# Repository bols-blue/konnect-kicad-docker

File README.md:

# konnect-kicad-docker

Konnect(KiCad 用 MCP サーバ)と KiCad 10 の CLI を 1 イメージに同梱し、
Claude Code から **回路図生成 → ERC → 製造ファイル出力** まで回すための検証環境。

PCB のインタラクティブ編集(部品配置・配線)は KiCad の GUI プロセスを必要とする。
ローカルのデスクトップ環境では `make gui` で同じイメージの KiCad GUI を X11 転送で
起動し、その IPC ソケットを Konnect と共有することで PCB 系ツールも使える。

## 使い方(Claude Code)

プラグイン `kicad-konnect` として入れると、どのディレクトリでも使える。

```bash
# 1. Docker イメージを取得 (初回のみ)
docker pull ghcr.io/bols-blue/konnect-kicad:10
docker tag ghcr.io/bols-blue/konnect-kicad:10 konnect-kicad:10

# 2. プラグインをインストール (Claude Code 内の /plugin からでも可)
claude plugin marketplace add bols-blue/konnect-kicad-docker
claude plugin install kicad-konnect@konnect-kicad

# 3. 作業ディレクトリで起動 (このディレクトリがコンテナの /work になる)
mkdir -p ~/kicad-work && cd ~/kicad-work && git init
claude
```

1. `/mcp` で `plugin:kicad-konnect:konnect` が connected になっていることを確認する
2. 「/work/demo に KiCad プロジェクトを作って、抵抗を 1 つ置いて ERC して」のように頼む
   - KiCad の話をすればスキルは自動で読み込まれる
   - `/kicad-konnect:kicad-konnect` で明示的に呼ぶこともできる

**作業領域の指定:**
- `/work` にする場所は `KONNECT_PROJECTS=/path/to/dir claude` で変えられる
- ホームディレクトリ直下や `/` で起動すると、安全のため konnect は起動しない

**PCB 編集・自動配線(GUI が必要):** 次の順で操作する。起動コマンドは Claude に聞けば、インストール先のパスで教えてくれる。
1. プラグインの `scripts/kicad-gui.sh /work/<name>/<name>.kicad_pro` で KiCad GUI を起動する
2. PCB エディタで基板を開く
3. `/mcp` で konnect を再接続する
   - native Specctra ブリッジ(自動配線用の DSN 出力・SES 取り込み)を使うときは必須
   - GUI を起動し直したら、再接続もやり直す

**更新:** `claude plugin marketplace update konnect-kicad` のあと、プラグインを入れ直す。

**このリポジトリの中ではプラグインは不要:**
- ルートの `.mcp.json` とスキルへのリンクで動く(`/work` は `./projects`)
- プラグインを入れたままここで起動すると konnect が 2 つ立つので、`/plugin` で無効にする

Codex で使う場合や、構成の詳細は後述の「プラグインとして使う」を参照。

## 前提

- Docker(Compose v2 同梱のもの)、Linux x86_64(KiCad 公式イメージが amd64 のみ)
- ディスク空き 3 GB 程度(公開イメージを使う場合)/ 10 GB 程度(自前ビルドの場合)
- Claude Code

## セットアップ

公開イメージを使う(推奨):

```bash
make pull      # ghcr.io/bols-blue/konnect-kicad:10 を取得し konnect-kicad:10 としてタグ付け
make smoke     # 疎通確認
```

自前でビルドする:

```bash
make build     # 初回は Rust のフルビルドを含むため時間がかかる
make smoke
```

`make smoke` が全項目 OK になったら、このディレクトリで Claude Code を起動する。
`.mcp.json` がプロジェクトスコープの MCP 設定として読み込まれ、`konnect` サーバが
使えるようになる(初回は MCP サーバの承認プロンプトが出る)。

```bash
claude
```

Claude Code 側の動き方はスキル `plugins/kicad-konnect/skills/kicad-konnect/` に
書いてある(このリポジトリでは `.claude/skills/` から読み込まれる)。これが本体。
リポジトリ固有の約束は `CLAUDE.md`。

## プラグインとして使う(Claude Code / Codex)

このリポジトリは Claude Code と Codex のプラグインマーケットプレイスを兼ねている。
プラグイン `kicad-konnect` を入れると、どのディレクトリでもスキルと `konnect`
MCP サーバが使える。Docker イメージは別途必要(上の `make pull`、または
`docker pull ghcr.io/bols-blue/konnect-kicad:10 && docker tag ghcr.io/bols-blue/konnect-kicad:10 konnect-kicad:10`)。

Claude Code:

```bash
claude plugin marketplace add bols-blue/konnect-kicad-docker
claude plugin install kicad-konnect@konnect-kicad
```

Codex:

```bash
codex plugin marketplace add bols-blue/konnect-kicad-docker
# Codex の /plugins から kicad-konnect をインストール
```

**`/work` にマウントされるのはエージェントを起動したディレクトリ。** 環境変数
`KONNECT_PROJECTS` で上書きできる。ホームディレクトリ直下や `/` では安全のため
起動を拒否する。

- Claude Code: 起動ディレクトリ(`CLAUDE_PROJECT_DIR`)が既定
- Codex: MCP サーバがプラグインのディレクトリで起動されるため、起動ディレクトリを
  知る手段が無い。**`KONNECT_PROJECTS` の設定が必須**
  (例: `KONNECT_PROJECTS=$PWD codex`)。
  シェルのサンドボックスが Docker ソケットを塞ぐ
  (`permission denied while trying to connect to the docker API`、codex-cli 0.160.1 で確認)。
  `kicad-cli.sh` の実行時にサンドボックス外での実行を承認する
- Codex: konnect の MCP ツール呼び出しには承認が要る。`codex exec`(非対話)では
  承認できず `MCP tool call requires approval, but approval policy is never` で失敗する。
  `default_tools_approval_mode = "auto"` を設定しても変わらなかった。対話モードで使うこと

| 構成要素 | 場所 |
| --- | --- |
| Claude Code の manifest(MCP 設定込み) | `plugins/kicad-konnect/.claude-plugin/plugin.json` |
| Codex の manifest / MCP 設定 | `plugins/kicad-konnect/.codex-plugin/plugin.json` / `codex-mcp.json` |
| スキル | `plugins/kicad-konnect/skills/kicad-konnect/` |
| マーケットプレイス | `.claude-plugin/marketplace.json`(Claude Code)/ `.agents/plugins/marketplace.json`(Codex) |

IPC ソケットと GUI 設定は `~/.local/state/konnect-kicad/` に置く
(`KONNECT_IPC_DIR` / `KONNECT_GUI_CONFIG` で変更可)。

## ディレクトリ

```
.
├── Dockerfile              KiCad 公式イメージ + Konnect ビルド + Freerouting/Java
├── docker-compose.yml      バッチ用ワークベンチ(任意)
├── Makefile                pull / build / smoke / shell / gui
├── .github/workflows/      イメージのビルド・smoke test・GHCR 公開
├── .mcp.json               このリポジトリで作業するときの MCP 設定
├── CLAUDE.md               このリポジトリ固有の約束
├── .claude-plugin/         Claude Code のマーケットプレイス定義
├── .agents/plugins/        Codex のマーケットプレイス定義
├── .claude/skills/         スキルへのシンボリックリンク
├── plugins/kicad-konnect/  プラグイン本体
│   ├── .claude-plugin/     Claude Code の manifest
│   ├── .codex-plugin/      Codex の manifest (+ codex-mcp.json)
│   ├── skills/kicad-konnect/  スキル(可否の線引き・ルール・手順・既知の癖)
│   └── scripts/
│       ├── _env.sh         作業領域・IPC の場所の決定(共通)
│       ├── konnect-mcp.sh  MCP stdio 起動ラッパー
│       ├── kicad-cli.sh    ホストから kicad-cli を叩くラッパー
│       ├── kicad-gui.sh    KiCad GUI を X11 転送で起動 (PCB系ツール用)
│       └── smoke-test.sh   疎通確認
└── projects/               作業領域。make / .mcp.json 経由ではコンテナの /work にマウントされる
```

**このリポジトリでは、ホストの `./projects` がコンテナの `/work`。** Konnect に渡すパスは常に
`/work/...` 形式にする。

既存の KiCad プロジェクトを試すときは `projects/` の下に `git clone` する。
`projects/*/` はこのリポジトリの `.gitignore` で除外しているので、クローンした
リポジトリはそれ自身の git で管理する。ライブラリの絶対パスや KiCad 6 以前の
ファイル形式など、取り込み時に直すべき点はスキルの `references/import-existing.md` にまとめてある。

```bash
cd projects && git clone <repo-url>
```

## 設計上のポイント

**ランタイムに KiCad 公式イメージを使っている。** 公式イメージは kicad-cli 利用を
想定して配布されており、GUI 用途はサポート対象外と明示されている。この環境は
まさに CLI だけを使うので用途が一致する。

**Konnect はソースからビルドしている。** 配布バイナリは Windows / macOS 向けで、
Linux は公式にはロードマップ段階(コード自体は 3 プラットフォームで CI を通過)。
ビルダーはランタイム (Debian 13 trixie) より古い bookworm にして、新しい glibc 上で
そのまま動くバイナリにしている。

**グローバル `sym-lib-table` をイメージに焼いてある。** コンテナは毎回まっさらな
HOME で起動するため、これが無いとシンボル解決に失敗して ERC が通らない。
`make smoke` の項目 2 がここを見ている。

**コンテナは呼び出し元の UID で起動する。** ラッパースクリプトが
`--user $(id -u):$(id -g)` を渡しているので、`./projects` に root 所有の
ファイルが生えない。

## 事前に把握しておくべき制約

**PCB 系ツールは GUI 起動中のみ。** Konnect の PCB 編集は KiCad 10 の IPC API
(NNG + protobuf)経由で、KiCad が対象基板を PCB エディタで開いた状態で
動いている必要がある。

```bash
make gui PROJECT=/work/demo/demo.kicad_pro   # KiCad が X11 (Wayland なら XWayland) で開く
# → プロジェクトマネージャで PCB エディタを開く
make gui-stop
```

- IPC ソケットはホストの `./.kicad-ipc`(プラグインとして使うときは `~/.local/state/konnect-kicad/ipc`)を GUI / Konnect 両コンテナの
  `/tmp/kicad` にマウントして共有する。Konnect には `KICAD_API_SOCKET` で固定パスを渡す
  (Konnect のソケット自動検出は起動時に一度だけなので、GUI を後から起動しても繋がるように)
- GUI の設定は `./.kicad-gui-config`(プラグインでは `~/.local/state/konnect-kicad/gui-config`)に永続化する。初回だけセットアップウィザードが出る
  (完了するまで IPC サーバが起動しない)
- 公式イメージの GUI 利用はサポート外。フォント・IME・OpenGL で問題が出る可能性がある
- 動作確認済み: 回路図 → PCB 反映、フットプリント配置、外形追加、保存、
  DSN 出力 → Freerouting → SES 取り込み → DRC の通し(THT 部品の基板)。
  SMD 受動部品 (roundrect パッド) は Konnect が DSN 出力を拒否するので、
  DSN 出力と SES 取り込みは GUI で人が行う。詳細はスキルの可否表
- 自動配線は Freerouting 2.3.0(SHA-256 検証済み)+ OpenJDK 25 をイメージに同梱。
  Konnect が headless MCP モードで起動し、DSN → SES をローカルで処理する。
  起動時に GitHub へ新版チェックの通信が出る(`KONNECT_NETWORK=none` なら出ないが部品検索も止まる)
- ヘッドレス環境(SSH 先など)ではこの経路は使えない。回路図と ERC まで作って、
  あとはホストの KiCad に引き継ぐ

**Konnect は beta。** コアのツールチェーンは動作確認済みだが若いリリースで、
実地での検証を求めている段階。回路図ファイルを直接書き換えるので、必ず git 管理下の
コピーに対して使うこと。実案件のディレクトリを `./projects` にマウントしない。

**Konnect のライセンスは AGPL-3.0。** ホビイスト・学生・フリーランス・OSS は自由に使える一方、
企業の場合は Konnect の上や周辺に作ったものが、ネットワーク越しに提供する
ソフトウェアも含めて同ライセンスでのオープンソース化を要求される。商用ライセンスも
別途用意されている。個人の評価で閉じるなら問題にならないが、社内共有や業務利用に
広げる前に法務確認を入れること(法的判断は専門家に)。

**HTTP モードは有効にしていない。** Konnect のサーバには認証が無く、ツールは
ファイルを編集し kicad-cli を実行するため、上流でも compose はループバック限定で
公開している。この構成では stdio のみにしている。必要になったら認証付きの
リバースプロキシを前段に置き、`0.0.0.0` に素で公開しないこと。

## バージョン

中身のバージョンは Dockerfile の `ARG` 既定値で固定している(動作検証済みの組み合わせ)。

| 部品 | バージョン | 定義 |
| --- | --- | --- |
| KiCad | 10.0.6 | `KICAD_TAG` |
| Konnect | `9d582b6` (0.12.1) | `KONNECT_REF`(ブランチ・タグ・SHA いずれも可) |
| Freerouting | 2.3.0 | `FREEROUTING_VERSION` / `FREEROUTING_SHA256` |
| OpenJDK | 25 (Debian パッケージ) | Dockerfile |

別の組み合わせを試す場合:

```bash
make build KICAD_TAG=10.0.7 KONNECT_REF=<タグ or コミットSHA>
make smoke
```

検証できたら Dockerfile の既定値を更新して main に push すると、GitHub Actions が
smoke test を通したうえで GHCR に公開する。ビルド済みイメージのバージョンは
`make versions` で確認できる。

## 公開イメージ

`ghcr.io/bols-blue/konnect-kicad` に以下のタグで公開している
(`.github/workflows/image.yml`)。

| タグ | 内容 |
| --- | --- |
| `10` | main の最新 |
| `kicad<ver>-konnect<sha7>` | 中身のバージョンで固定したい場合 |
| `sha-<sha7>` | このリポジトリのコミット |
| `v*` | リリースタグ |

## 同梱ソフトウェアのライセンスとソース

イメージは以下を再配布している。いずれもソースは上流で公開されており、
同梱したバージョンは上の表とイメージのラベル(`docker inspect`)で特定できる。

| 部品 | ライセンス | ソース |
| --- | --- | --- |
| Konnect | AGPL-3.0-only | https://github.com/mixelpixx/Konnect (該当コミットは `/etc/konnect-commit.txt`) |
| KiCad | GPL-3.0-or-later | https://gitlab.com/kicad/code/kicad (ベースイメージ `kicad/kicad`) |
| Freerouting | GPL-3.0 | https://github.com/freerouting/freerouting |
| OpenJDK | GPL-2.0 with Classpath Exception | Debian パッケージ `openjdk-25-jre-headless` |
| Debian ベースの各パッケージ | 各パッケージによる | `apt-get source` で取得可 |

このリポジトリ自体(Dockerfile・スクリプト・ドキュメント)には上記のコードは含まれない。

## トラブルシュート

| 症状 | 対処 |
| --- | --- |
| `make build` がライブラリ検証で落ちる | KiCad イメージのディレクトリ構成が変わっている。エラー出力の `ls` 結果を見て Dockerfile のパスを修正 |
| Claude Code が konnect を認識しない | `claude mcp list` で状態を確認。`.mcp.json` の相対パスはプロジェクトルート基準。ダメなら `plugins/kicad-konnect/scripts/konnect-mcp.sh` を絶対パスに書き換える |
| `image not found` | `make pull` / `make build` 未実行、または `KONNECT_IMAGE` の値が `.mcp.json` と不一致 |
| ERC でシンボルが軒並み見つからない | `make smoke` の項目 2 を確認。`sym-lib-table=NO` なら Dockerfile の `KICAD_CONFIG_VER` を実際の設定ディレクトリ名に合わせる |
| `IPC connect failed` | KiCad GUI 未起動、または PCB エディタで対象基板を開いていない。`make gui`。プラグインとこのリポジトリの `.mcp.json` では IPC の置き場が違うので、GUI も同じ側から起動する |
| `make gui` で IPC ソケットが現れない | 初回ウィザードやダイアログで止まっていないか確認。`KONNECT_GUI_DEBUG=1 make gui` で前面実行 |
| `make` が「ターゲットを make するルールがありません」 | `projects/` の下で実行している。`make -C <このリポジトリ> gui ...` |
| クローンしたプロジェクトで ERC がライブラリ不足で大量に落ちる | プロジェクトの `sym-lib-table` / `fp-lib-table` がホストの絶対パスを指している。ライブラリをプロジェクト内にコピーし `${KIPRJMOD}` 基準にする |
| Konnect の回路図編集が `stale_target` で拒否される | KiCad 6 以前の回路図。KiCad GUI で開いて保存する(`kicad-cli sch upgrade` では直らない) |
| Rust ビルドが OOM で落ちる | Docker Desktop のメモリ割り当てを 8 GB 以上に |

## 参考

- Konnect: https://github.com/mixelpixx/Konnect
- KiCad 公式 Docker イメージ: https://www.kicad.org/download/docker/

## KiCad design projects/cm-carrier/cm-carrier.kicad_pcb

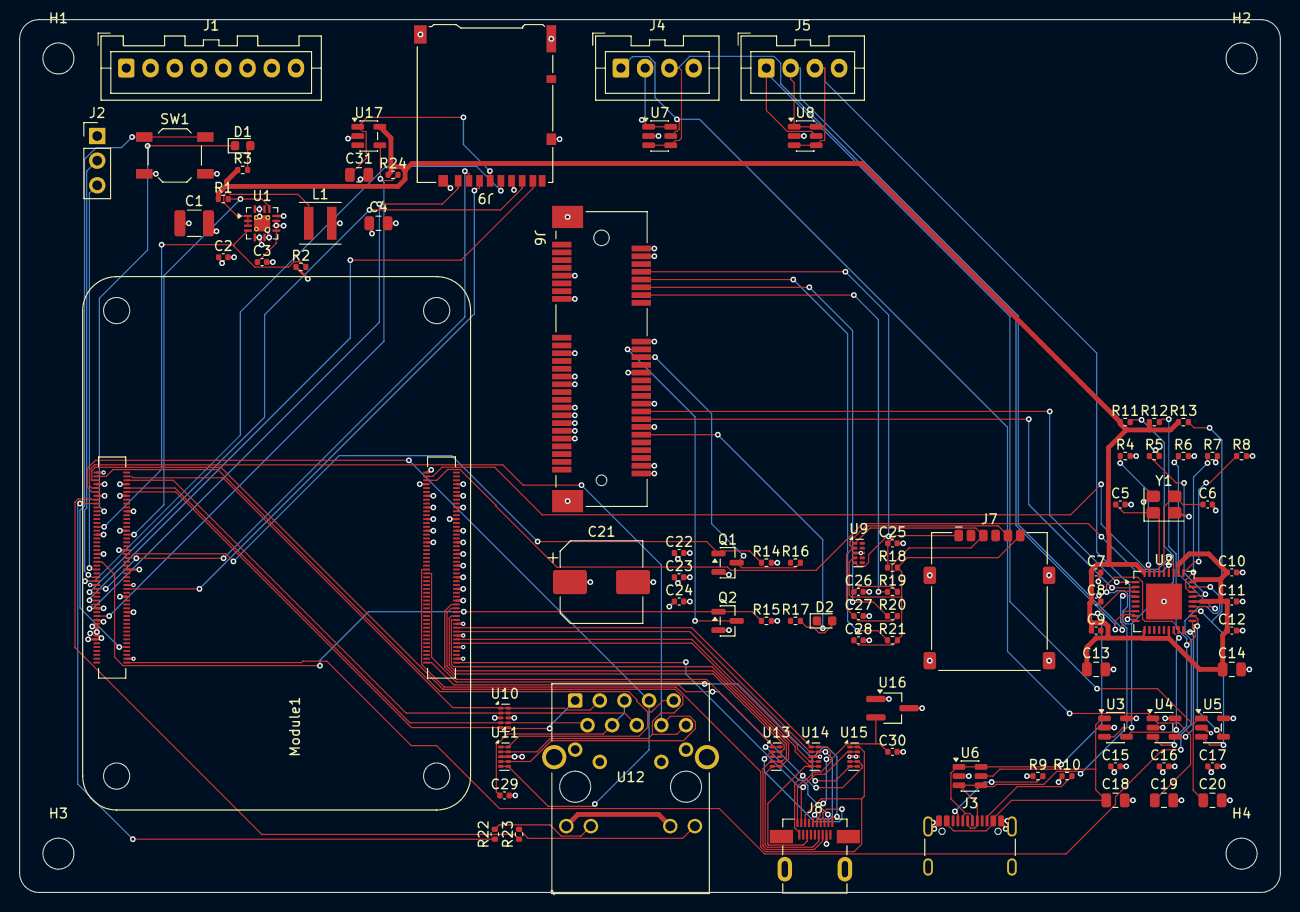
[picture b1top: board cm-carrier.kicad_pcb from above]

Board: 4 copper layers, 130.0 x 90.0 mm, 93 parts (0 on the bottom side), 89 nets.

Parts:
C1: 10uF 25V; C_1210_3225Metric
C2, C7, C8, C9, C10, C11, C12, C22, C25, C29, C30: 100nF; C_0402_1005Metric
C3: 3.3nF; C_0402_1005Metric
C4: 22uF 6.3V; C_0805_2012Metric
C5, C6: 27pF; C_0402_1005Metric
C13, C14, C18, C19, C20: 10uF 10V; C_0805_2012Metric
C15, C16, C17: 1uF 10V; C_0402_1005Metric
C21: 470uF; CP_Elec_8x10
C23, C26, C27, C28: 33pF; C_0402_1005Metric
C24: 10pF; C_0402_1005Metric
C31: 10uF; C_0805_2012Metric
D1: LED_ACT green; LED_0603_1608Metric
D2: green; LED_0603_1608Metric
H1, H2, H3, H4: MountingHole_3.2mm_M3
J1: XA_5V_IN; JST_XA_B08B-XASK-1_1x08_P2.50mm_Vertical
J2: DEBUG_UART; PinHeader_1x03_P2.54mm_Vertical
J3: USB_C_HOST (USB2.0); USB_C_Receptacle_GCT_USB4105-xx-A_16P_TopMnt_Horizontal
J4: XA_USB1; JST_XA_B04B-XASK-1_1x04_P2.50mm_Vertical
J5: XA_USB2; JST_XA_B04B-XASK-1_1x04_P2.50mm_Vertical
J6: EC25-J Mini PCIe; BUS_PCI_Express_Mini_Full
J7: nanoSIM; nanoSIM_GCT_SIM8060-6-0-14-00
J8: micro HDMI (Type D); HDMI_Micro-D_Molex_46765-2xxx
J9: microSD; microSD_HC_Hirose_DM3AT-SF-PEJM5
L1: 2.2uH XFL4020-222MEB; L_Coilcraft_XxL4020
Module1: CM4/CM5 (Lite); Raspberry-Pi-5-Compute-Module
Q1, Q2: 2N7002; SOT-23
R1, R2, R14, R15: 100k; R_0402_1005Metric
R3, R17: 1k; R_0402_1005Metric
R4: 12k 1%; R_0402_1005Metric
R5, R6, R7, R8: 36k 1%; R_0402_1005Metric
R9, R10: 56k; R_0402_1005Metric
R11, R12, R13, R16: 10k; R_0402_1005Metric
R18: 15k; R_0402_1005Metric
R19, R20, R21: 0R; R_0402_1005Metric
R22, R23: 470R; R_0402_1005Metric
R24: 10k 1%; R_0402_1005Metric
SW1: PWR_BUT; SW_SPST_TL3342
U1: TPS62132; VQFN-16-1EP_3x3mm_P0.5mm_EP1.68x1.68mm_ThermalVias
U2: USB2514B-I/M2; QFN-36-1EP_6x6mm_P0.5mm_EP3.7x3.7mm
U3, U4, U5: TPS2051CDBV; SOT-23-5
U6, U7, U8: USBLC6-2SC6; SOT-23-6
U9: TPD4E05U06DQA; USON-10_2.5x1.0mm_P0.5mm
U10, U11, U13, U14, U15: TPD4EUSB30; USON-10_2.5x1.0mm_P0.5mm
U12: MagJack A70-112-331N126; TRJG0926HENL
U16: RT9742SNGV; TSOT-23_HandSoldering
U17: RT9742GGJ5; SOT-23-5
Y1: 24MHz CL=18pF; Crystal_SMD_3225-4Pin_3.2x2.5mm

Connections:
+3V3: C7.1, C8.1, C9.1, C10.1, C11.1, C12.1, C13.1, C14.1, Module1.78 (GPIO_VREF(1.8v/3.3v_Input)), Module1.84 (+3.3v_(Output)), Module1.86 (+3.3v_(Output)), R1.1, R3.1, R11.1, R12.1, R13.1, R24.1, U2.5 (VDDA33), U2.10 (VDDA33), U2.15 (VDD33), U2.23 (VDD33), U2.27 (VBUS_DET), U2.29 (VDDA33), U2.36 (VDDA33), U12.15 (LEDY_A), U12.17 (LEDG_A), U17.5 (IN)
+3V3_LTE: C4.1, C21.1, C22.1, C23.1, C24.1, J6.2 (+3V3AUX), J6.39 (+3V3AUX), J6.41 (+3V3AUX), J6.52 (+3V3AUX), L1.2, R2.1, R16.1, R17.1, U1.14 (VOS)
+5V: C1.1, C2.1, C15.1, C16.1, C17.1, J1.1, J1.2, J1.3, J1.4, Module1.77 (+5v_(Input)), Module1.79 (+5v_(Input)), Module1.81 (+5v_(Input)), Module1.83 (+5v_(Input)), Module1.85 (+5v_(Input)), Module1.87 (+5v_(Input)), R9.1, R10.1, U1.10 (VIN), U1.11 (VIN), U1.12 (VIN), U3.5 (IN), U4.5 (IN), U5.5 (IN), U16.1 (IN)
/CM/LED_nACT: D1.1 (K), Module1.21 (LED_nACT)
/CM/PWR_BUT: Module1.92 (PWR_BUT), SW1.1
/CM/UART_RXD: J2.3, Module1.51 (GPIO15)
/CM/UART_TXD: J2.2, Module1.55 (GPIO14)
/IO (Ethernet, HDMI, microSD)/ETH_CT: C29.1, U12.4 (CT), U12.5 (CT)
/IO (Ethernet, HDMI, microSD)/ETH_LEDG_K: R23.2, U12.18 (LEDG_K)
/IO (Ethernet, HDMI, microSD)/ETH_LEDY_K: R22.2, U12.16 (LEDY_K)
/IO (Ethernet, HDMI, microSD)/HDMI_5V: C30.1, J8.19 (+5V), U16.2 (OUT)
/IO (Ethernet, HDMI, microSD)/SD_VDD: C31.1, J9.4 (VDD), U17.1 (OUT)
/LTE/LED_WWAN_N: D2.1 (K), J6.42 (~LED_WWAN)
/LTE/LTE_PERST_N: J6.22 (~PERST), Q1.3 (D), R16.2
/LTE/LTE_W_DISABLE_N: J6.20 (~W_DISABLE), Q2.3 (D)
/LTE/USIM_CLK: C27.1, J7.3 (CLK), R20.2, U9.2 (D1-)
/LTE/USIM_CLK_M: J6.12 (UIM_CLK), R20.1
/LTE/USIM_DATA: C28.1, J7.7 (I/O), R18.2, R21.2, U9.4 (D2+)
/LTE/USIM_DATA_M: J6.10 (UIM_DATA), R21.1
/LTE/USIM_RST: C26.1, J7.2 (RST), R19.2, U9.1 (D1+)
/LTE/USIM_RST_M: J6.14 (~UIM_RESET), R19.1
/LTE/USIM_VDD: C25.1, J6.8 (UIM_PWR), J7.1 (VCC), R18.1, U9.5 (D2-)
/Power/LTE_SS: C3.1, U1.9 (SS/TR)
/USB Hub/HUB_CFG_SEL0: R5.1, U2.24 (SCL/SMBCLK/CFG_SEL0)
/USB Hub/HUB_CFG_SEL1: R7.1, U2.25 (HS_IND/CFG_SEL1)
/USB Hub/HUB_NON_REM0: R8.1, U2.28 (SUSP_IND/LOCAL_PWR/NON_REM0)
/USB Hub/HUB_NON_REM1: R6.1, U2.22 (SDA/SMBDATA/NON_REM1)
/USB Hub/HUB_RBIAS: R4.1, U2.35 (RBIAS)
/USB Hub/HUB_XTALIN: C5.1, U2.33 (XTALIN/CLKIN), Y1.1
/USB Hub/HUB_XTALOUT: C6.1, U2.32 (XTALOUT), Y1.3
/USB Hub/P2_CC1: J3.A5 (CC1), R9.2
/USB Hub/P2_CC2: J3.B5 (CC2), R10.2
/USB Hub/P2_DM: J3.A7 (D-), J3.B7 (D-), U2.3 (USBDM_DN2/PRT_DIS_M2), U6.1 (I/O1), U6.6 (I/O1)
/USB Hub/P2_DP: J3.A6 (D+), J3.B6 (D+), U2.4 (USBDP_DN2/PRT_DIS_P2), U6.3 (I/O2), U6.4 (I/O2)
/USB Hub/P2_OCS_N: R11.2, U2.17 (OCS_N2), U3.3 (~FLT)
/USB Hub/P2_PWR: U2.16 (PRTPWR2/BC_EN2), U3.4 (EN)
/USB Hub/P2_VBUS: C18.1, J3.A4 (VBUS), J3.A9 (VBUS), J3.B4 (VBUS), J3.B9 (VBUS), U3.1 (OUT), U6.5 (VBUS)
/USB Hub/P3_DM: J4.2, U2.6 (USBDM_DN3/PRT_DIS_M3), U7.1 (I/O1), U7.6 (I/O1)
/USB Hub/P3_DP: J4.3, U2.7 (USBDP_DN3/PRT_DIS_P3), U7.3 (I/O2), U7.4 (I/O2)
/USB Hub/P3_OCS_N: R12.2, U2.19 (OCS_N3), U4.3 (~FLT)
/USB Hub/P3_PWR: U2.18 (PRTPWR3/BC_EN3), U4.4 (EN)
/USB Hub/P3_VBUS: C19.1, J4.1, U4.1 (OUT), U7.5 (VBUS)
/USB Hub/P4_DM: J5.2, U2.8 (USBDM_DN4/PRT_DIS_M4), U8.1 (I/O1), U8.6 (I/O1)
/USB Hub/P4_DP: J5.3, U2.9 (USBDP_DN4/PRT_DIS_P4), U8.3 (I/O2), U8.4 (I/O2)
/USB Hub/P4_OCS_N: R13.2, U2.21 (OCS_N4), U5.3 (~FLT)
/USB Hub/P4_PWR: U2.20 (PRTPWR4/BC_EN4), U5.4 (EN)
/USB Hub/P4_VBUS: C20.1, J5.1, U5.1 (OUT), U8.5 (VBUS)
ETH_LED2_N: Module1.17 (Ethernet_nLED2(3.3v)), R22.1
ETH_LED3_N: Module1.15 (Ethernet_nLED3(3.3v)), R23.1
ETH_P0_N: Module1.10 (Ethernet_Pair0_N), U10.4 (D2+), U10.7, U12.2 (TRD0-)
ETH_P0_P: Module1.12 (Ethernet_Pair0_P), U10.5 (D2-), U10.6, U12.1 (TRD0+)
ETH_P1_N: Module1.6 (Ethernet_Pair1_N), U10.2 (D1-), U10.9, U12.6 (TRD1-)
ETH_P1_P: Module1.4 (Ethernet_Pair1_P), U10.1 (D1+), U10.10, U12.3 (TRD1+)
ETH_P2_N: Module1.9 (Ethernet_Pair2_N), U11.4 (D2+), U11.7, U12.8 (TRD2-)
ETH_P2_P: Module1.11 (Ethernet_Pair2_P), U11.5 (D2-), U11.6, U12.7 (TRD2+)
ETH_P3_N: Module1.5 (Ethernet_Pair3_N), U11.2 (D1-), U11.9, U12.10 (TRD3-)
ETH_P3_P: Module1.3 (Ethernet_Pair3_P), U11.1 (D1+), U11.10, U12.9 (TRD3+)
GND: C1.2, C2.2, C3.2, C4.2, C5.2, C6.2, C7.2, C8.2, C9.2, C10.2, C11.2, C12.2, C13.2, C14.2, C15.2, C16.2, C17.2, C18.2, C19.2, C20.2, C21.2, C22.2, C23.2, C24.2, C25.2, C26.2, C27.2, C28.2, C29.2, C30.2, C31.2, J1.5, J1.6, J1.7, J1.8, J2.1, J3.A1 (GND), J3.A12 (GND), J3.B1 (GND), J3.B12 (GND), J3.SH (SHIELD), J4.4, J5.4, J6.4 (GND), J6.9 (GND), J6.15 (GND), J6.18 (GND), J6.21 (GND), J6.26 (GND), J6.27 (GND), J6.29 (GND), J6.34 (GND), J6.35 (GND), J6.37 (GND), J6.40 (GND), J6.43 (GND), J6.50 (GND), J6.MP, J7.5 (GND), J7.SH, J8.4 (D2S), J8.7 (D1S), J8.10 (D0S), J8.13 (CKS), J8.16 (GND), J8.SH, J9.6 (VSS), J9.SH (SHIELD), Module1.1 (GND), Module1.2 (GND), Module1.7 (GND), Module1.8 (GND), Module1.13 (GND), Module1.14 (GND), Module1.22 (GND), Module1.23 (GND), Module1.32 (GND), Module1.33 (GND), Module1.42 (GND), Module1.43 (GND), Module1.52 (GND), Module1.53 (GND), Module1.59 (GND), Module1.60 (GND), Module1.65 (GND), Module1.66 (GND), Module1.71 (GND), Module1.74 (GND), Module1.98 (GND), Module1.101 (USB_OTG_ID), Module1.107 (GND), Module1.108 (GND), Module1.113 (GND), Module1.114 (GND), Module1.119 (GND), Module1.120 (GND), Module1.125 (GND), Module1.126 (GND), Module1.131 (GND), Module1.132 (GND), Module1.137 (GND), Module1.138 (GND), Module1.144 (GND), Module1.150 (GND), Module1.155 (GND), Module1.156 (GND), Module1.161 (GND), Module1.162 (GND), Module1.167 (GND), Module1.168 (GND), Module1.173 (GND), Module1.174 (GND), Module1.179 (GND), Module1.180 (GND), Module1.185 (GND), Module1.186 (GND), Module1.191 (GND), Module1.192 (GND), Module1.197 (GND), Module1.198 (GND), Q1.2 (S), Q2.2 (S), R4.2, R5.2, R6.2, R7.2, R8.2, R14.2, R15.2, SW1.2, U1.5 (FB), U1.6 (GND), U1.7 (FSW), U1.8 (DEF), U1.15 (GND), U1.16 (GND), U1.17 (GND), U2.37 (VSS), U3.2 (GND), U4.2 (GND), U5.2 (GND), U6.2 (GND), U7.2 (GND), U8.2 (GND), U9.3 (GND), U9.8 (GND), U10.3 (GND), U10.8 (GND), U11.3 (GND), U11.8 (GND), U12.19 (SHIELD), U12.20 (SHIELD), U13.3 (GND), U13.8 (GND), U14.3 (GND), U14.8 (GND), U15.3 (GND), U15.8 (GND), U16.3 (GND), U17.2 (GND), Y1.2 (G), Y1.4 (G)
HDMI0_CEC: J8.15 (CEC), Module1.151 (HDMI0_CEC), U15.1 (D1+), U15.10
HDMI0_CK_N: J8.14 (CK-), Module1.190 (HDMI0_CLK_N), U14.5 (D2-), U14.6
HDMI0_CK_P: J8.12 (CK+), Module1.188 (HDMI0_CLK_P), U14.4 (D2+), U14.7
HDMI0_D0_N: J8.11 (D0-), Module1.184 (HDMI0_TX0_N), U14.2 (D1-), U14.9
HDMI0_D0_P: J8.9 (D0+), Module1.182 (HDMI0_TX0_P), U14.1 (D1+), U14.10
HDMI0_D1_N: J8.8 (D1-), Module1.178 (HDMI0_TX1_N), U13.5 (D2-), U13.6
HDMI0_D1_P: J8.6 (D1+), Module1.176 (HDMI0_TX1_P), U13.4 (D2+), U13.7
HDMI0_D2_N: J8.5 (D2-), Module1.172 (HDMI0_TX2_N), U13.2 (D1-), U13.9
HDMI0_D2_P: J8.3 (D2+), Module1.170 (HDMI0_TX2_P), U13.1 (D1+), U13.10
HDMI0_HPD: J8.1 (HPD/HEAC-), Module1.153 (HDMI0_HOTPLUG), U15.5 (D2-), U15.6
HDMI0_SCL: J8.17 (SCL), Module1.200 (HDMI0_SCL), U15.2 (D1-), U15.9
HDMI0_SDA: J8.18 (SDA), Module1.199 (HDMI0_SDA), U15.4 (D2+), U15.7
HUB_RESET_N: Module1.100 (CAM_GPIO1), U2.26 (RESET_N)
LTE_3V3_PG: Module1.29 (GPIO16), R2.2, U1.4 (PG)
LTE_AIRPLANE: Module1.47 (GPIO23), Q2.1 (G), R15.1
LTE_PWR_EN: Module1.34 (GPIO5), R1.2, U1.13 (EN)
LTE_RESET: Module1.46 (GPIO22), Q1.1 (G), R14.1
LTE_USB_N: J6.36 (USB_D-), U2.1 (USBDM_DN1/PRT_DIS_M1)
LTE_USB_P: J6.38 (USB_D+), U2.2 (USBDP_DN1/PRT_DIS_P1)
unnamed: D1.2 (A), R3.2
unnamed: D2.2 (A), R17.2
unnamed: L1.1, U1.1 (SW), U1.2 (SW), U1.3 (SW)
SD_CLK: J9.5 (CLK), Module1.57 (SD_CLK)
SD_CMD: J9.3 (CMD), Module1.62 (SD_CMD)
SD_DAT0: J9.7 (DAT0), Module1.63 (SD_DAT0)
SD_DAT1: J9.8 (DAT1), Module1.67 (SD_DAT1)
SD_DAT2: J9.1 (DAT2), Module1.69 (SD_DAT2)
SD_DAT3: J9.2 (DAT3/CD), Module1.61 (SD_DAT3)
SD_PWR_ON: Module1.75 (SD_PWR_ON), R24.2, U17.4 (EN)
USB_HOST_N: Module1.103 (USB2_N), U2.30 (USBDM_UP)
USB_HOST_P: Module1.105 (USB2_P), U2.31 (USBDP_UP)

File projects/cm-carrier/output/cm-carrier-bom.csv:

"Refs","Value","Footprint","Qty","Description"
"C1","10uF 25V","Capacitor_SMD:C_1210_3225Metric","1","Unpolarized capacitor"
"C2,C7-C12,C22,C25,C29,C30","100nF","Capacitor_SMD:C_0402_1005Metric","11","Unpolarized capacitor"
"C3","3.3nF","Capacitor_SMD:C_0402_1005Metric","1","Unpolarized capacitor"
"C4","22uF 6.3V","Capacitor_SMD:C_0805_2012Metric","1","Unpolarized capacitor"
"C5,C6","27pF","Capacitor_SMD:C_0402_1005Metric","2","Unpolarized capacitor"
"C13,C14,C18-C20","10uF 10V","Capacitor_SMD:C_0805_2012Metric","5","Unpolarized capacitor"
"C15-C17","1uF 10V","Capacitor_SMD:C_0402_1005Metric","3","Unpolarized capacitor"
"C21","470uF","Capacitor_SMD:CP_Elec_8x10","1","470uF 6.3V low-ESR conductive polymer (Quectel EC25 Mini PCIe HW Design 3.2)"
"C23,C26-C28","33pF","Capacitor_SMD:C_0402_1005Metric","4","Unpolarized capacitor"
"C24","10pF","Capacitor_SMD:C_0402_1005Metric","1","Unpolarized capacitor"
"C31","10uF","Capacitor_SMD:C_0805_2012Metric","1","Unpolarized capacitor"
"D1","LED_ACT green","LED_SMD:LED_0603_1608Metric","1","Light emitting diode"
"D2","green","LED_SMD:LED_0603_1608Metric","1","Light emitting diode"
"J1","XA_5V_IN","Connector_JST:JST_XA_B08B-XASK-1_1x08_P2.50mm_Vertical","1","Generic connector, single row, 01x08, script generated (kicad-library-utils/schlib/autogen/connector/)"
"J2","DEBUG_UART","Connector_PinHeader_2.54mm:PinHeader_1x03_P2.54mm_Vertical","1","Generic connector, single row, 01x03, script generated (kicad-library-utils/schlib/autogen/connector/)"
"J3","USB_C_HOST (USB2.0)","Connector_USB:USB_C_Receptacle_GCT_USB4105-xx-A_16P_TopMnt_Horizontal","1","USB 2.0-only 16P Type-C Receptacle connector"
"J4","XA_USB1","Connector_JST:JST_XA_B04B-XASK-1_1x04_P2.50mm_Vertical","1","Generic connector, single row, 01x04, script generated (kicad-library-utils/schlib/autogen/connector/)"
"J5","XA_USB2","Connector_JST:JST_XA_B04B-XASK-1_1x04_P2.50mm_Vertical","1","Generic connector, single row, 01x04, script generated (kicad-library-utils/schlib/autogen/connector/)"
"J6","EC25-J Mini PCIe","Connector_PCBEdge:BUS_PCI_Express_Mini_Full","1","Mini-PCI Express bus connector"
"J7","nanoSIM","Connector_Card:nanoSIM_GCT_SIM8060-6-0-14-00","1","SIM Card"
"J8","micro HDMI (Type D)","Connector_Video:HDMI_Micro-D_Molex_46765-2xxx","1","HDMI 1.4+ type D connector"
"J9","microSD","Connector_Card:microSD_HC_Hirose_DM3AT-SF-PEJM5","1","Micro SD Card Socket with card detection pins"
"L1","2.2uH XFL4020-222MEB","Inductor_SMD:L_Coilcraft_XxL4020","1","Inductor"
"Module1","CM4/CM5 (Lite)","CM5IO:Raspberry-Pi-5-Compute-Module","1","RaspberryPi Compute module 5"
"Q1,Q2","2N7002","Package_TO_SOT_SMD:SOT-23","2","0.115A Id, 60V Vds, N-Channel MOSFET, SOT-23"
"R1,R2,R14,R15","100k","Resistor_SMD:R_0402_1005Metric","4","Resistor"
"R3,R17","1k","Resistor_SMD:R_0402_1005Metric","2","Resistor"
"R4","12k 1%","Resistor_SMD:R_0402_1005Metric","1","Resistor"
"R5-R8","36k 1%","Resistor_SMD:R_0402_1005Metric","4","Resistor"
"R9,R10","56k","Resistor_SMD:R_0402_1005Metric","2","Resistor"
"R11-R13,R16","10k","Resistor_SMD:R_0402_1005Metric","4","Resistor"
"R18","15k","Resistor_SMD:R_0402_1005Metric","1","Resistor"
"R19-R21","0R","Resistor_SMD:R_0402_1005Metric","3","Resistor"
"R22,R23","470R","Resistor_SMD:R_0402_1005Metric","2","Resistor"
"R24","10k 1%","Resistor_SMD:R_0402_1005Metric","1","Resistor"
"SW1","PWR_BUT","Button_Switch_SMD:SW_SPST_TL3342","1","Push button switch, generic, two pins"
"U1","TPS62132","Package_DFN_QFN:VQFN-16-1EP_3x3mm_P0.5mm_EP1.68x1.68mm_ThermalVias","1","3A Step-Down Converter with DCS-Control, Fixed 3.3V Output Voltage, 3-17V Input Voltage, QFN-16"
"U2","USB2514B-I/M2","Package_DFN_QFN:QFN-36-1EP_6x6mm_P0.5mm_EP3.7x3.7mm","1","USB 2.0 Hi-Speed Hub Controller"
"U3-U5","TPS2051CDBV","Package_TO_SOT_SMD:SOT-23-5","3","0.5A Current limited power switch, single channel, output discharge, reverse blocking, SOT-23-5"
"U6-U8","USBLC6-2SC6","Package_TO_SOT_SMD:SOT-23-6","3","Very low capacitance ESD protection diode, 2 data-line, SOT-23-6"
"U9","TPD4E05U06DQA","Package_SON:USON-10_2.5x1.0mm_P0.5mm","1","4-Channel ESD Protection for Super-Speed USB 3.0 Interface, USON-10"
"U10,U11,U13-U15","TPD4EUSB30","Package_SON:USON-10_2.5x1.0mm_P0.5mm","5","4-Channel ESD Protection for Super-Speed USB 3.0 Interface, USON-10"
"U12","MagJack A70-112-331N126","CM5IO:TRJG0926HENL","1",""
"U16","RT9742SNGV","Package_TO_SOT_SMD:TSOT-23_HandSoldering","1","500mA Load Switch"
"U17","RT9742GGJ5","Package_TO_SOT_SMD:SOT-23-5","1","1A load switch"
"Y1","24MHz CL=18pF","Crystal:Crystal_SMD_3225-4Pin_3.2x2.5mm","1","Four pin crystal, GND on pins 2 and 4"

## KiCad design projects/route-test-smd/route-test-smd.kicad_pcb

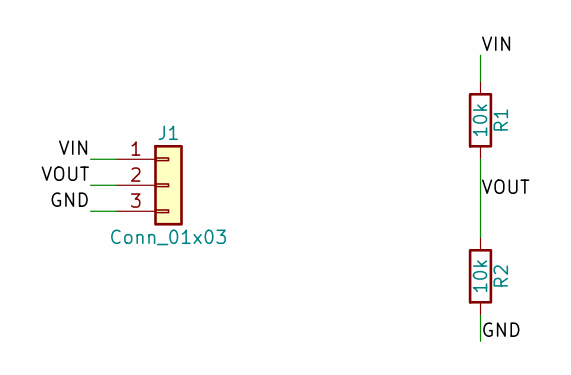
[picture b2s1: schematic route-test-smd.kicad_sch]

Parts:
J1: Conn_01x03; PinHeader_1x03_P2.54mm_Vertical
R1, R2: 10k; R_0805_2012Metric

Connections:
/GND: J1.3, R2.2
/VIN: J1.1, R1.1
/VOUT: J1.2, R1.2, R2.1

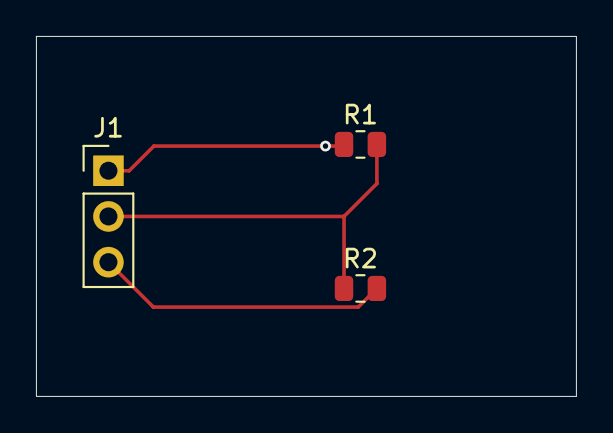
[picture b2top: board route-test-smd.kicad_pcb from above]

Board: 2 copper layers, 30.0 x 20.0 mm, 3 parts (0 on the bottom side), 3 nets.
